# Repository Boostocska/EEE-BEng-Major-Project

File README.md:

This project was being driven by the motivation to offer an alternative to the heating of homes based on the occupiers demands to save huge amounts of energy not only to save cost, but to also be more environmentally friendly and as a consequence, to relieve some of the stresses on the energy networks, which is all beneficial for the whole population.

The aim of the project was to build such a system that meets or exceeds these requirements to cut the costs – and subsequently the carbon emissions – of the households, where it is deployed by optimising the heating system’s control process adaptively. This product was aimed to be a proof-of-concept and be ready for further optimization for mass-production.

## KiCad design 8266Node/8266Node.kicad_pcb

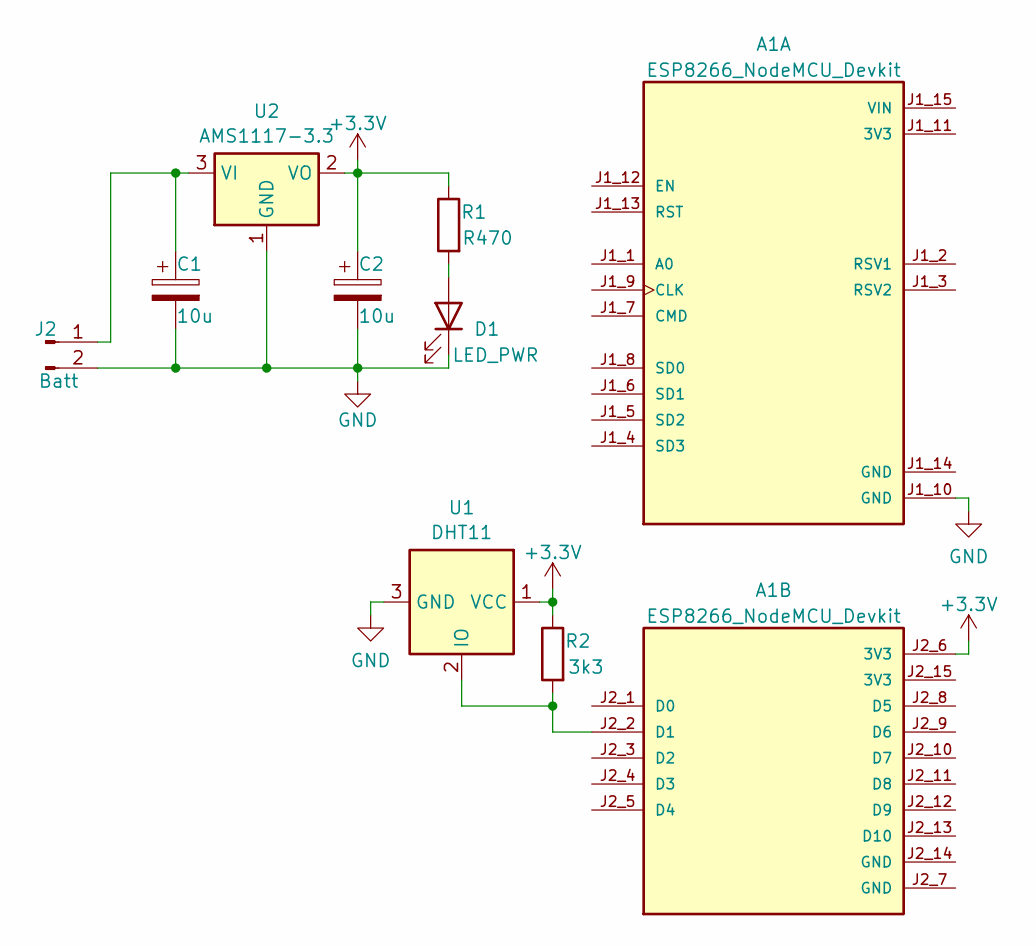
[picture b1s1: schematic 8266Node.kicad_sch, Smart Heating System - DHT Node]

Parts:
A1: ESP8266_NodeMCU_Devkit; PARTREV N/A
C1, C2: 10u; CP_Radial_D6.3mm_P2.50mm
D1: LED_PWR; LED_D3.0mm
J2: Batt; Molex_KK-254_AE-6410-02A_1x02_P2.54mm_Vertical
R1: R470; R_0805_2012Metric_Pad1.20x1.40mm_HandSolder
R2: 3k3; R_0805_2012Metric_Pad1.20x1.40mm_HandSolder
U1: DHT11; DHT11_Module
U2: AMS1117-3.3; SOT-223-3_TabPin2

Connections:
+3V3: A1.J2_6 (3V3), C2.1, R1.1, R2.1, U1.1 (VCC), U2.2 (VO)
GND: A1.J1_10 (GND), C1.2, C2.2, D1.1 (K), J2.2, U1.3 (GND), U2.1 (GND)
unnamed: A1.J2_2 (D1), R2.2, U1.2 (IO)
unnamed: D1.2 (A), R1.2
unnamed: C1.1, J2.1, U2.3 (VI)

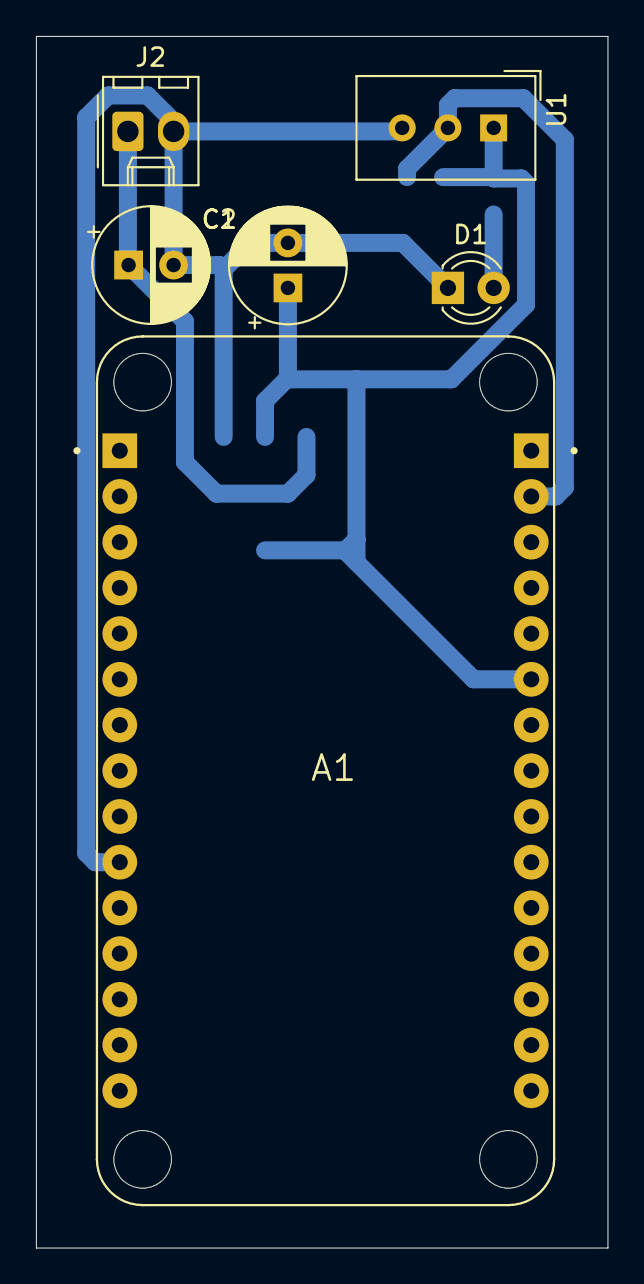
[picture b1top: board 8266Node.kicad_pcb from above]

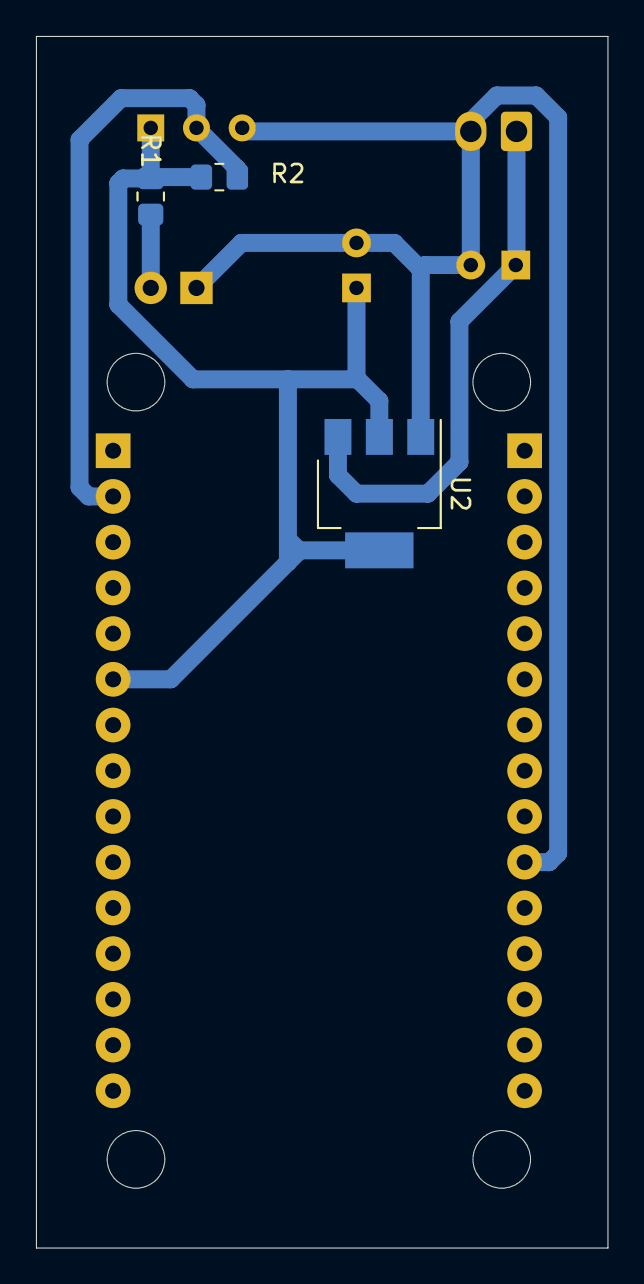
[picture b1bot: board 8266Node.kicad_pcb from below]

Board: 2 copper layers, 31.8 x 67.3 mm, 9 parts (3 on the bottom side), 5 nets.

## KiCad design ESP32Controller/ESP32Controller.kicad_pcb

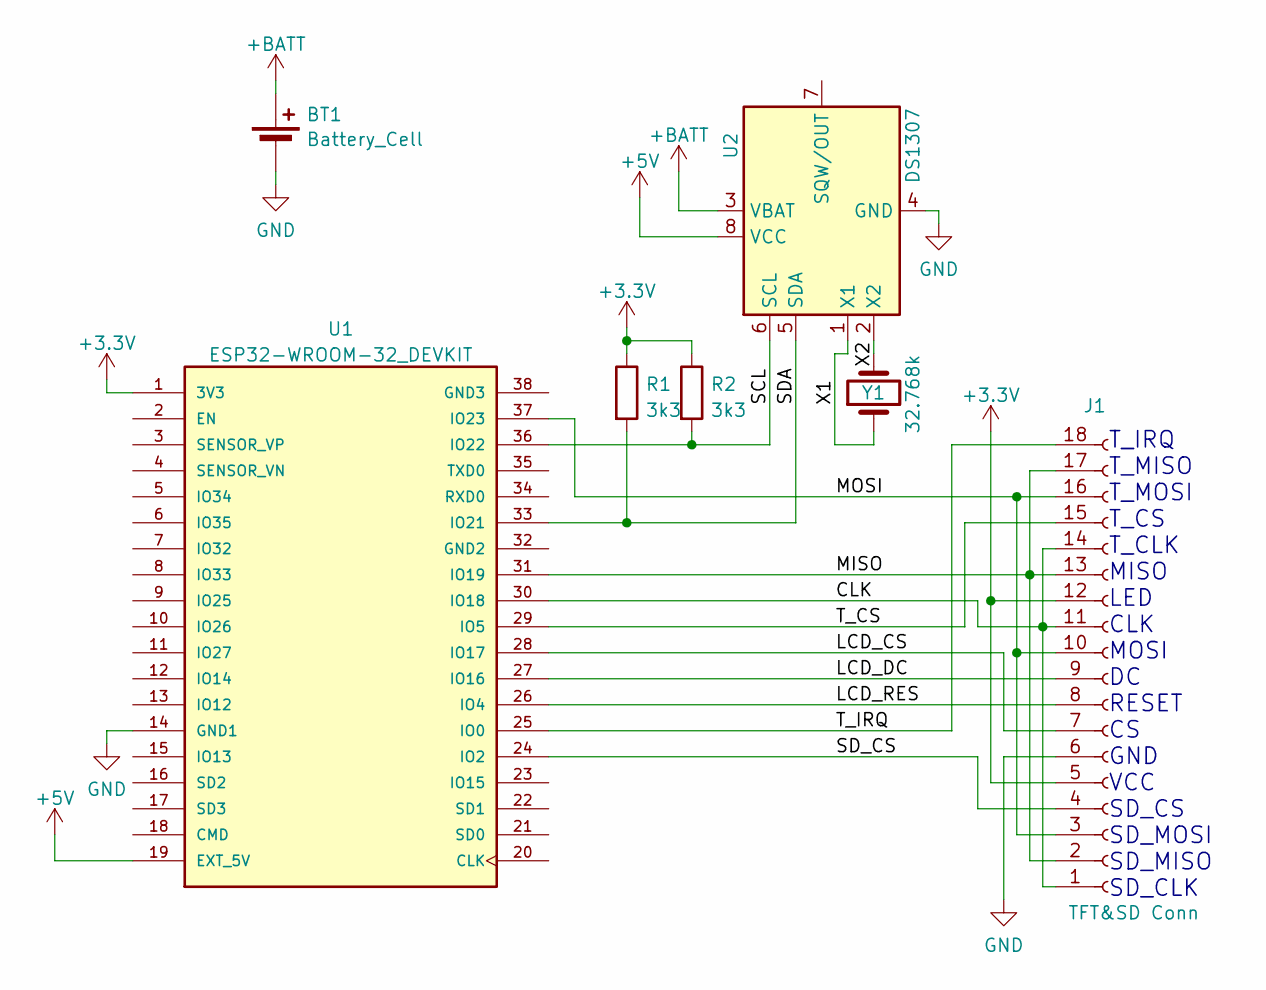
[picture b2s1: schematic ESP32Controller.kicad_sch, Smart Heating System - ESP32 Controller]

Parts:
BT1: Battery_Cell; BatteryHolder_Keystone_103_1x20mm
J1: TFT&SD Conn; 2.8LCDTouchWithSD
R1, R2: 3k3; R_Axial_DIN0207_L6.3mm_D2.5mm_P10.16mm_Horizontal
U1: ESP32-WROOM-32_DEVKIT; MODULE_ESP32-DEVKITC; PARTREV N/A
U2: DS1307; DIP-8_W7.62mm
Y1: 32.768k; Crystal_C38-LF_D3.0mm_L8.0mm_Horizontal

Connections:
+3V3: J1.5, J1.12, R1.1, R2.1, U1.1 (3V3)
+5V: U1.19 (EXT_5V), U2.8 (VCC)
+BATT: BT1.1 (+), U2.3 (VBAT)
/CLK: J1.1, J1.11, J1.14, U1.30 (IO18)
/LCD_CS: J1.7, U1.28 (IO17)
/LCD_DC: J1.9, U1.27 (IO16)
/LCD_RES: J1.8, U1.26 (IO4)
/MISO: J1.2, J1.13, J1.17, U1.31 (IO19)
/MOSI: J1.3, J1.10, J1.16, U1.37 (IO23)
/SCL: R2.2, U1.36 (IO22), U2.6 (SCL)
/SDA: R1.2, U1.33 (IO21), U2.5 (SDA)
/SD_CS: J1.4, U1.24 (IO2)
/T_CS: J1.15, U1.29 (IO5)
/T_IRQ: J1.18, U1.25 (IO0)
/X1: U2.1 (X1), Y1.1
/X2: U2.2 (X2), Y1.2
GND: BT1.2 (-), J1.6, U1.14 (GND1), U2.4 (GND)

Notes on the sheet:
T_IRQ T_MISO T_MOSI T_CS T_CLK MISO LED CLK MOSI DC RESET CS GND VCC SD_CS SD_MOSI SD_MISO SD_CLK

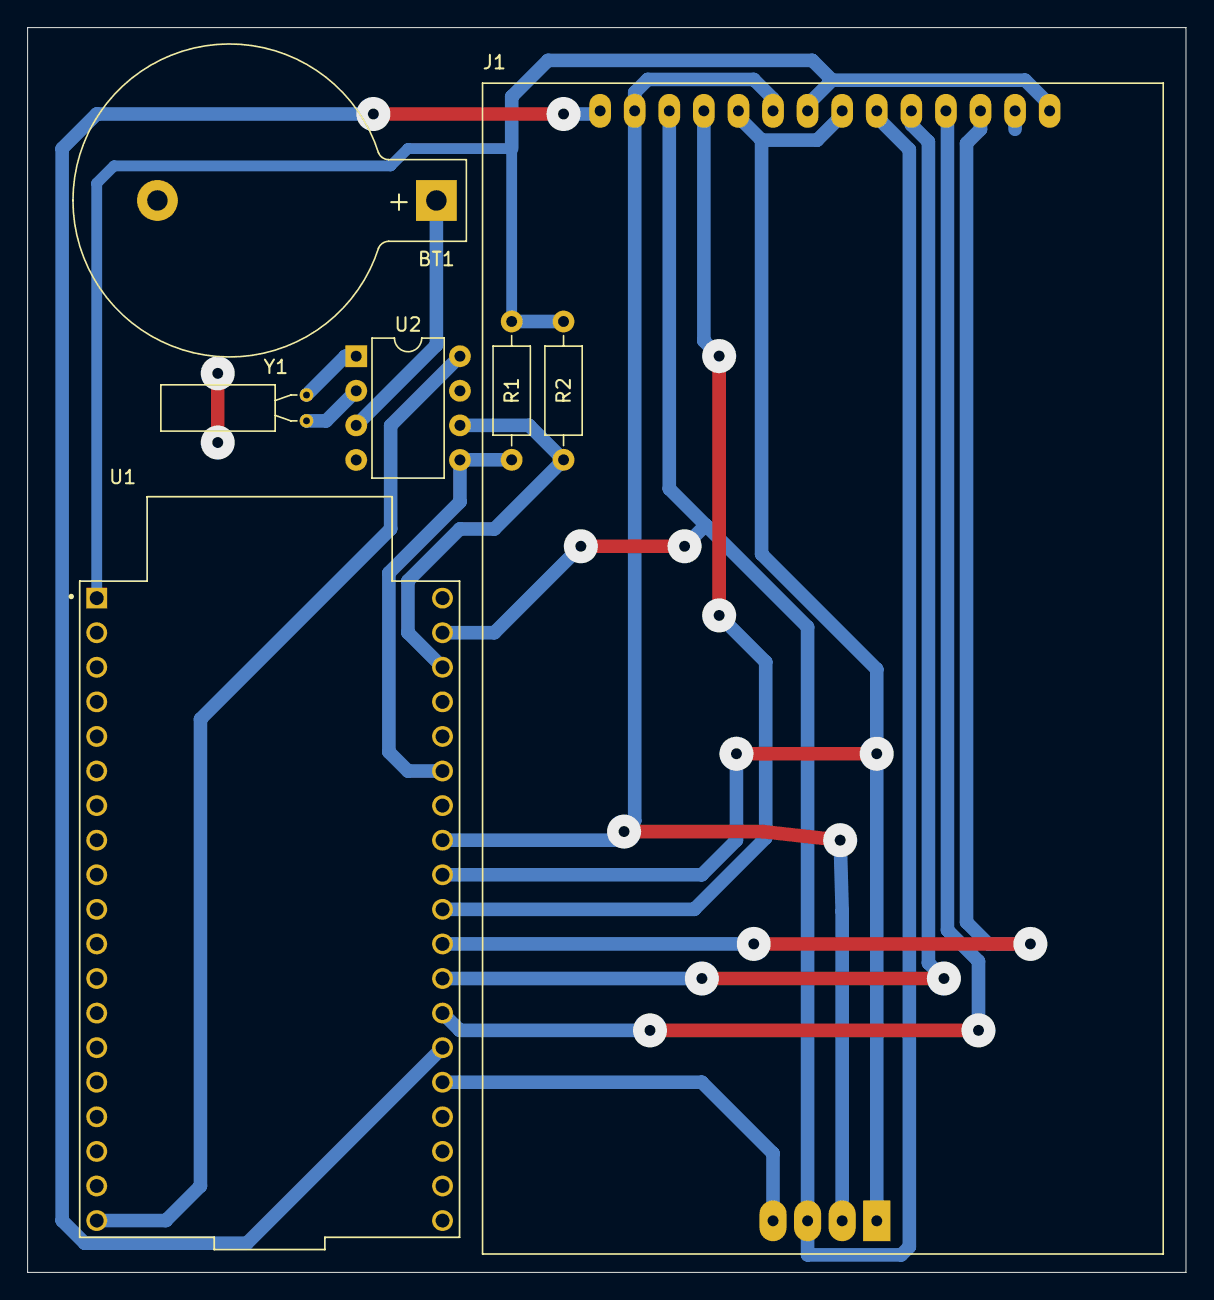
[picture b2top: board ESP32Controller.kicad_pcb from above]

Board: 2 copper layers, 85.1 x 91.4 mm, 7 parts (0 on the bottom side), 17 nets.

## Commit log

2024-03-04 Initial Release to Github
